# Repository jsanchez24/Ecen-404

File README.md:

# Ecen-404
Modulation Methods for Three-Phase Inverter

Control Subsystem
-avr_interface.v
-primary_side.v
-pulse.v
-pwm.v
-secondary_side.v
-serial_rx.v
-serial_tx.v
-spi_slave.v
-mojo_top.v

Sensor Subsytem
-Avanzato1.zip
-LM319.lbr
-LM319N.lbr
-Sensor Circuit.brb
-Sensor Circuit.sch
-TL081.lbr

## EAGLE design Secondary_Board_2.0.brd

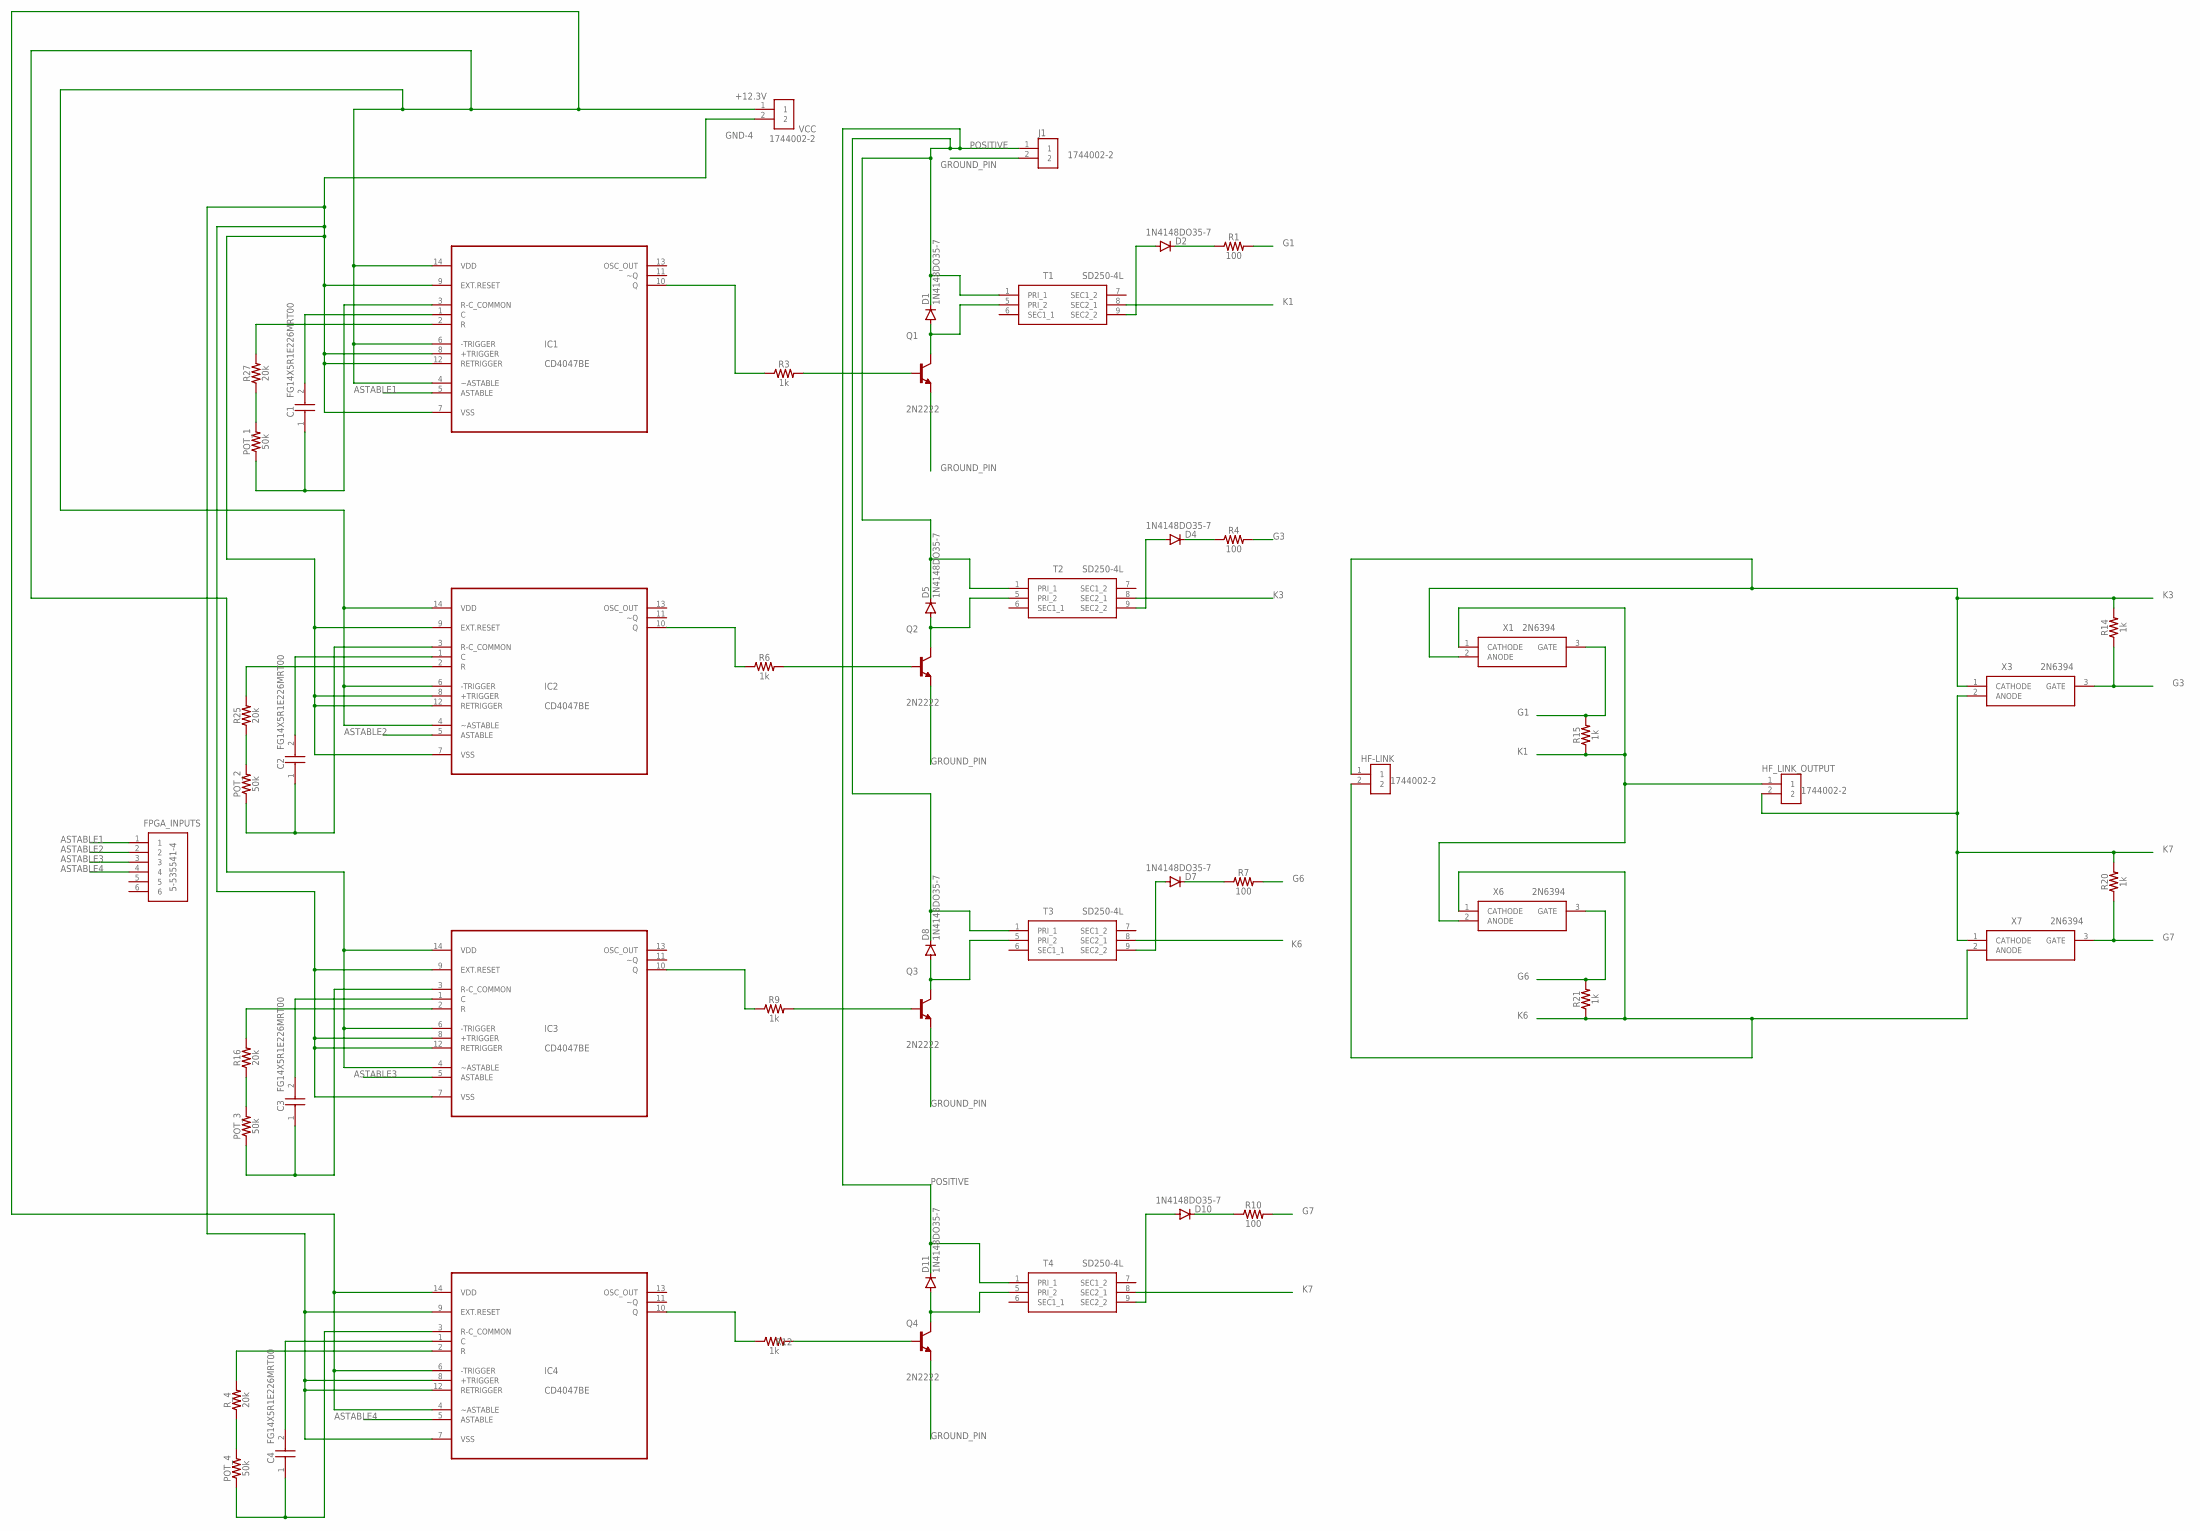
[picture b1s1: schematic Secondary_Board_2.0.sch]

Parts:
C1, C2, C3, C4: FG14X5R1E226MRT00; CAPPRD550W50D395H550
D1, D2, D4, D5, D7, D8, D10, D11: 1N4148DO35-7; DO35-7
FPGA_INPUTS: 5-535541-4; SHDR6W76P0X254_1X6_1524X356X62
HF-LINK: 1744002-2; CONN_1744002-2
HF_LINK_OUTPUT: 1744002-2; CONN_1744002-2
IC1, IC2, IC3, IC4: CD4047BE; DIP254P762X508-14
J1: 1744002-2; CONN_1744002-2
POT_1, POT_2, POT_3, POT_4: 50k; AXIAL-0.3
Q1, Q2, Q3, Q4: 2N2222; TO127P584H533-3
R1, R4, R7, R10: 100; AXIAL-0.3
R3, R6, R9, R12, R14, R15, R20, R21: 1k; AXIAL-0.3
R16, R25, R27: 20k; AXIAL-0.3
R_4: 20k; AXIAL-0.3
T1, T2, T3, T4: SD250-4L; SD2504L
VCC: 1744002-2; CONN_1744002-2
X1, X3, X6, X7: 2N6394; TO254P482X997X2018-3P

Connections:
+12.3V: IC1.4 (~ASTABLE), IC1.6 (-TRIGGER), IC1.14 (VDD), IC2.4 (~ASTABLE), IC2.6 (-TRIGGER), IC2.14 (VDD), IC3.4 (~ASTABLE), IC3.6 (-TRIGGER), IC3.14 (VDD), IC4.4 (~ASTABLE), IC4.6 (-TRIGGER), IC4.14 (VDD), VCC.1
ASTABLE1: FPGA_INPUTS.1, IC1.5 (ASTABLE)
ASTABLE2: FPGA_INPUTS.2, IC2.5 (ASTABLE)
ASTABLE3: FPGA_INPUTS.3, IC3.5 (ASTABLE)
ASTABLE4: FPGA_INPUTS.4, IC4.5 (ASTABLE)
G1: R1.P$2 (2), R15.P$2 (2), X1.3 (GATE)
G3: R4.P$2 (2), R14.P$1 (1), X3.3 (GATE)
G6: R7.P$2 (2), R21.P$2 (2), X6.3 (GATE)
G7: R10.P$2 (2), R20.P$1 (1), X7.3 (GATE)
GND-4: IC1.7 (VSS), IC1.8 (+TRIGGER), IC1.9 (EXT.RESET), IC1.12 (RETRIGGER), IC2.7 (VSS), IC2.8 (+TRIGGER), IC2.9 (EXT.RESET), IC2.12 (RETRIGGER), IC3.7 (VSS), IC3.8 (+TRIGGER), IC3.9 (EXT.RESET), IC3.12 (RETRIGGER), IC4.7 (VSS), IC4.8 (+TRIGGER), IC4.9 (EXT.RESET), IC4.12 (RETRIGGER), VCC.2
GROUND_PIN: J1.2, Q1.1 (E), Q2.1 (E), Q3.1 (E), Q4.1 (E)
K1: HF_LINK_OUTPUT.1, R15.P$1 (1), T1.8 (SEC2_1), X1.1 (CATHODE), X6.2 (ANODE)
K3: HF-LINK.1, R14.P$2 (2), T2.8 (SEC2_1), X1.2 (ANODE), X3.1 (CATHODE)
K6: HF-LINK.2, R21.P$1 (1), T3.8 (SEC2_1), X6.1 (CATHODE), X7.2 (ANODE)
K7: HF_LINK_OUTPUT.2, R20.P$2 (2), T4.8 (SEC2_1), X3.2 (ANODE), X7.1 (CATHODE)
unnamed: D5.A, Q2.3 (C), T2.5 (PRI_2)
unnamed: D1.A, Q1.3 (C), T1.5 (PRI_2)
unnamed: D2.C, R1.P$1 (1)
unnamed: IC1.10 (Q), R3.P$1 (1)
unnamed: Q1.2 (B), R3.P$2 (2)
unnamed: D4.A, T2.9 (SEC2_2)
unnamed: IC2.10 (Q), R6.P$1 (1)
unnamed: IC3.10 (Q), R9.P$1 (1)
unnamed: IC4.10 (Q), R12.P$1 (1)
unnamed: D4.C, R4.P$1 (1)
unnamed: D7.A, T3.9 (SEC2_2)
unnamed: Q2.2 (B), R6.P$2 (2)
unnamed: D10.A, T4.9 (SEC2_2)
unnamed: D2.A, T1.9 (SEC2_2)
unnamed: D8.A, Q3.3 (C), T3.5 (PRI_2)
unnamed: D7.C, R7.P$1 (1)
unnamed: IC1.2 (R), R27.P$2 (2)
unnamed: POT_1.P$2 (2), R27.P$1 (1)
unnamed: C1.2 (-), IC1.1 (C)
unnamed: C1.1 (+), IC1.3 (R-C_COMMON), POT_1.P$1 (1)
unnamed: IC2.2 (R), R25.P$2 (2)
unnamed: POT_2.P$2 (2), R25.P$1 (1)
unnamed: C2.2 (-), IC2.1 (C)
unnamed: Q3.2 (B), R9.P$2 (2)
unnamed: C2.1 (+), IC2.3 (R-C_COMMON), POT_2.P$1 (1)
unnamed: D11.A, Q4.3 (C), T4.5 (PRI_2)
unnamed: D10.C, R10.P$1 (1)
unnamed: IC3.2 (R), R16.P$2 (2)
unnamed: Q4.2 (B), R12.P$2 (2)
unnamed: POT_3.P$2 (2), R16.P$1 (1)
unnamed: C3.2 (-), IC3.1 (C)
unnamed: C3.1 (+), IC3.3 (R-C_COMMON), POT_3.P$1 (1)
unnamed: IC4.2 (R), R_4.P$2 (2)
unnamed: POT_4.P$2 (2), R_4.P$1 (1)
unnamed: C4.2 (-), IC4.1 (C)
unnamed: C4.1 (+), IC4.3 (R-C_COMMON), POT_4.P$1 (1)
POSITIVE: D1.C, D5.C, D8.C, D11.C, J1.1, T1.1 (PRI_1), T2.1 (PRI_1), T3.1 (PRI_1), T4.1 (PRI_1)

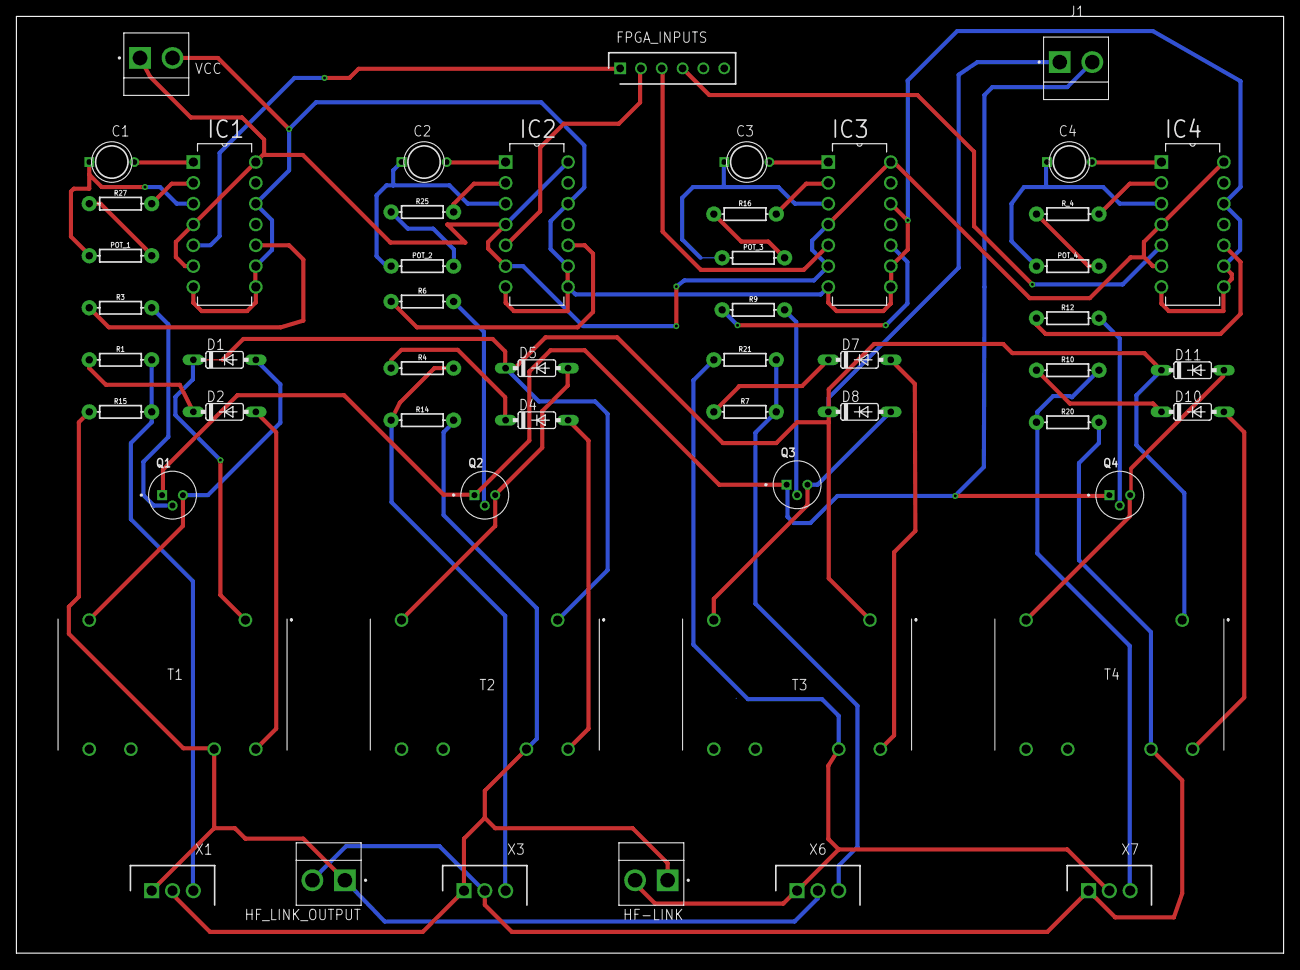
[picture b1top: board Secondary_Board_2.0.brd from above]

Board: 2 copper layers, 154.6 x 114.3 mm, 53 parts (0 on the bottom side), 52 nets.

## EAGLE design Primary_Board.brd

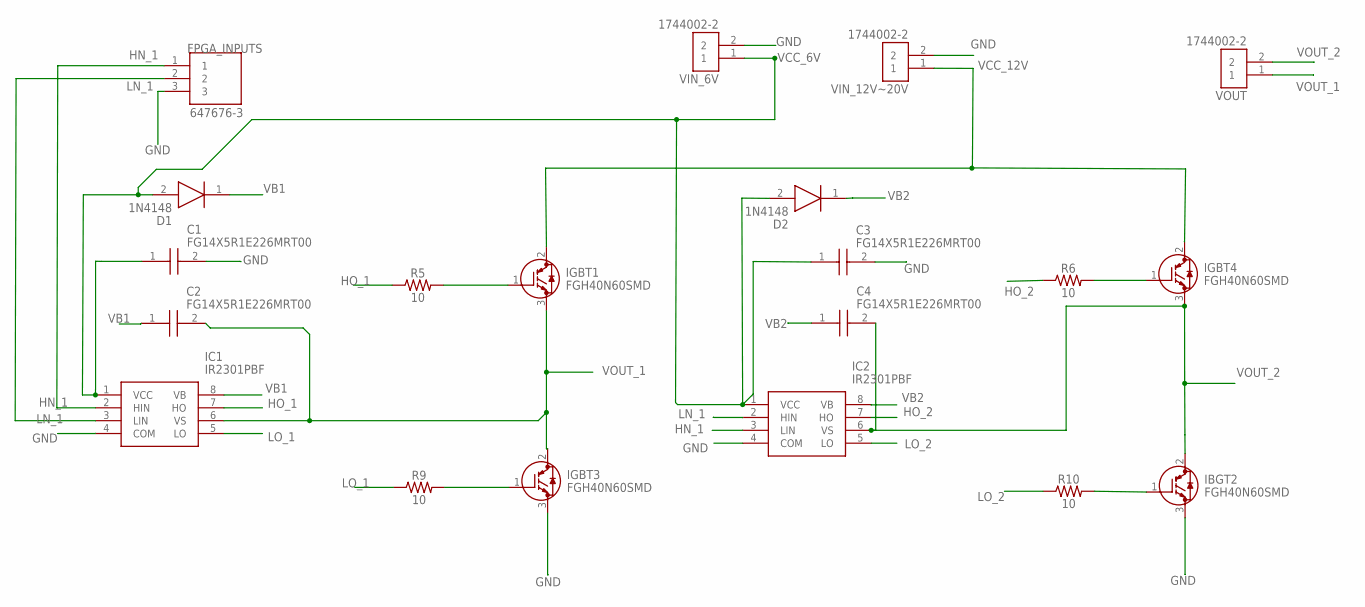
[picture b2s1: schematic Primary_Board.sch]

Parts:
C1, C2, C3, C4: FG14X5R1E226MRT00; CAPPRD550W50D395H550
D1, D2: 1N4148; DIOAD1068W53L380D172
FPGA_INPUTS: 647676-3; TE_647676-3
IBGT2: FGH40N60SMD; TO556P482X1562X2475-3P
IC1, IC2: IR2301PBF; DIP762W56P254L988H533Q8N
IGBT1, IGBT3, IGBT4: FGH40N60SMD; TO556P482X1562X2475-3P
R5, R6, R9, R10: 10; AXIAL-0.3
VIN_6V, VIN_12V~20V: 1744002-2; CONN_1744002-2
VOUT: 1744002-2; CONN_1744002-2

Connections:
GND: C1.2 (-), C3.2 (-), FPGA_INPUTS.3, IBGT2.3 (E), IC1.4 (COM), IC2.4 (COM), IGBT3.3 (E), VIN_6V.2, VIN_12V~20V.2
HN_1: FPGA_INPUTS.1, IC1.2 (HIN), IC2.3 (LIN)
HO_1: IC1.7 (HO), R5.P$1 (1)
HO_2: IC2.7 (HO), R6.P$1 (1)
IGBT2: IBGT2.1 (G), R10.P$2 (2)
LN_1: FPGA_INPUTS.2, IC1.3 (LIN), IC2.2 (HIN)
LO_1: IC1.5 (LO), R9.P$1 (1)
LO_2: IC2.5 (LO), R10.P$1 (1)
unnamed: IGBT1.1 (G), R5.P$2 (2)
unnamed: IGBT4.1 (G), R6.P$2 (2)
unnamed: IGBT3.1 (G), R9.P$2 (2)
VB1: C2.1 (+), D1.1 (K), IC1.8 (VB)
VB2: C4.1 (+), D2.1 (K), IC2.8 (VB)
VCC_6V: C1.1 (+), C3.1 (+), D1.2 (A), D2.2 (A), IC1.1 (VCC), IC2.1 (VCC), VIN_6V.1
VCC_12V: IGBT1.2 (C), IGBT4.2 (C), VIN_12V~20V.1
VOUT_1: C2.2 (-), IC1.6 (VS), IGBT1.3 (E), IGBT3.2 (C), VOUT.1
VOUT_2: C4.2 (-), IBGT2.2 (C), IC2.6 (VS), IGBT4.3 (E), VOUT.2

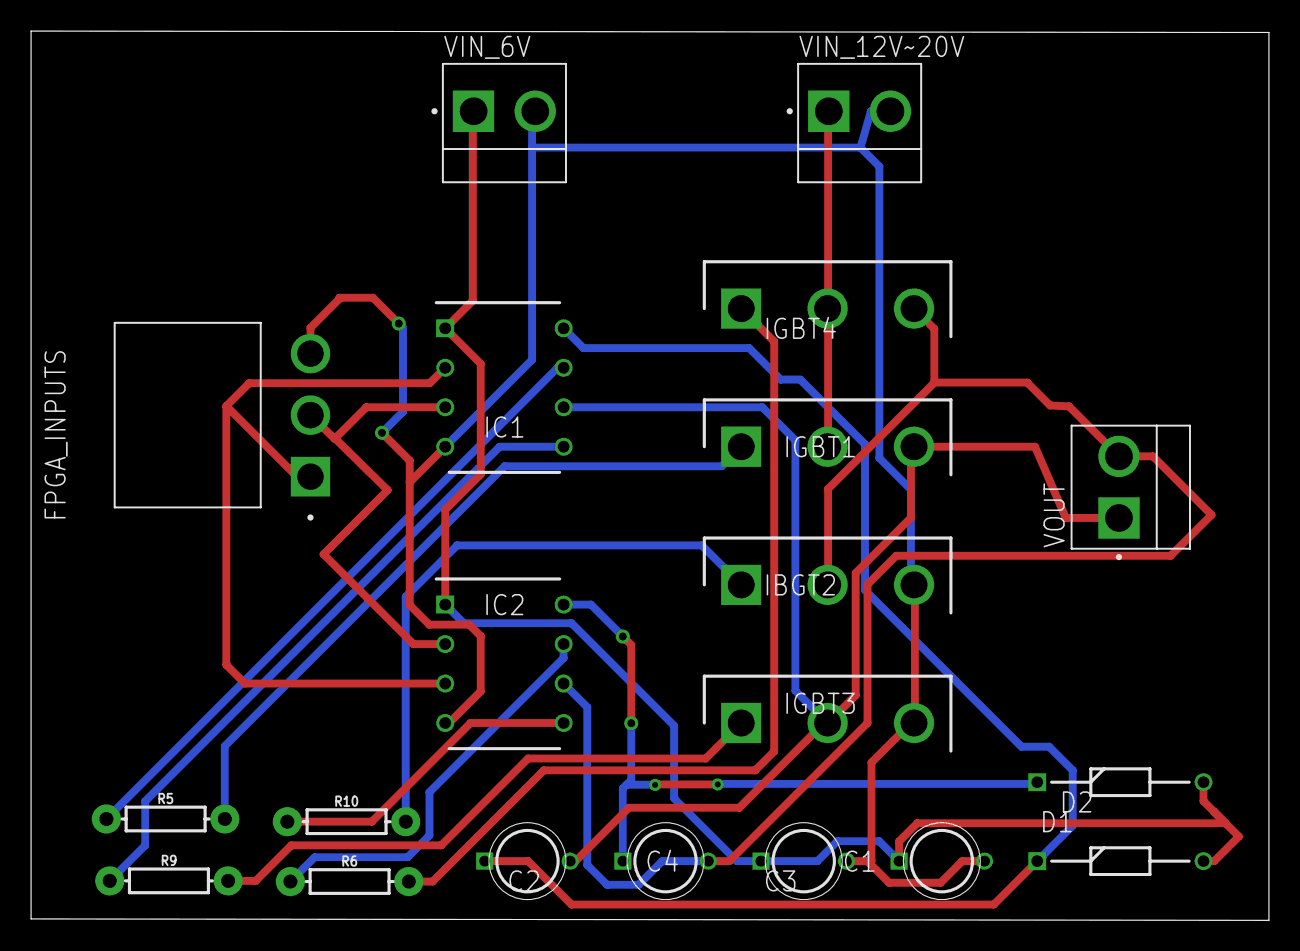
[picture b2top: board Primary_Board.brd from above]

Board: 2 copper layers, 79.7 x 57.2 mm, 20 parts (0 on the bottom side), 17 nets.

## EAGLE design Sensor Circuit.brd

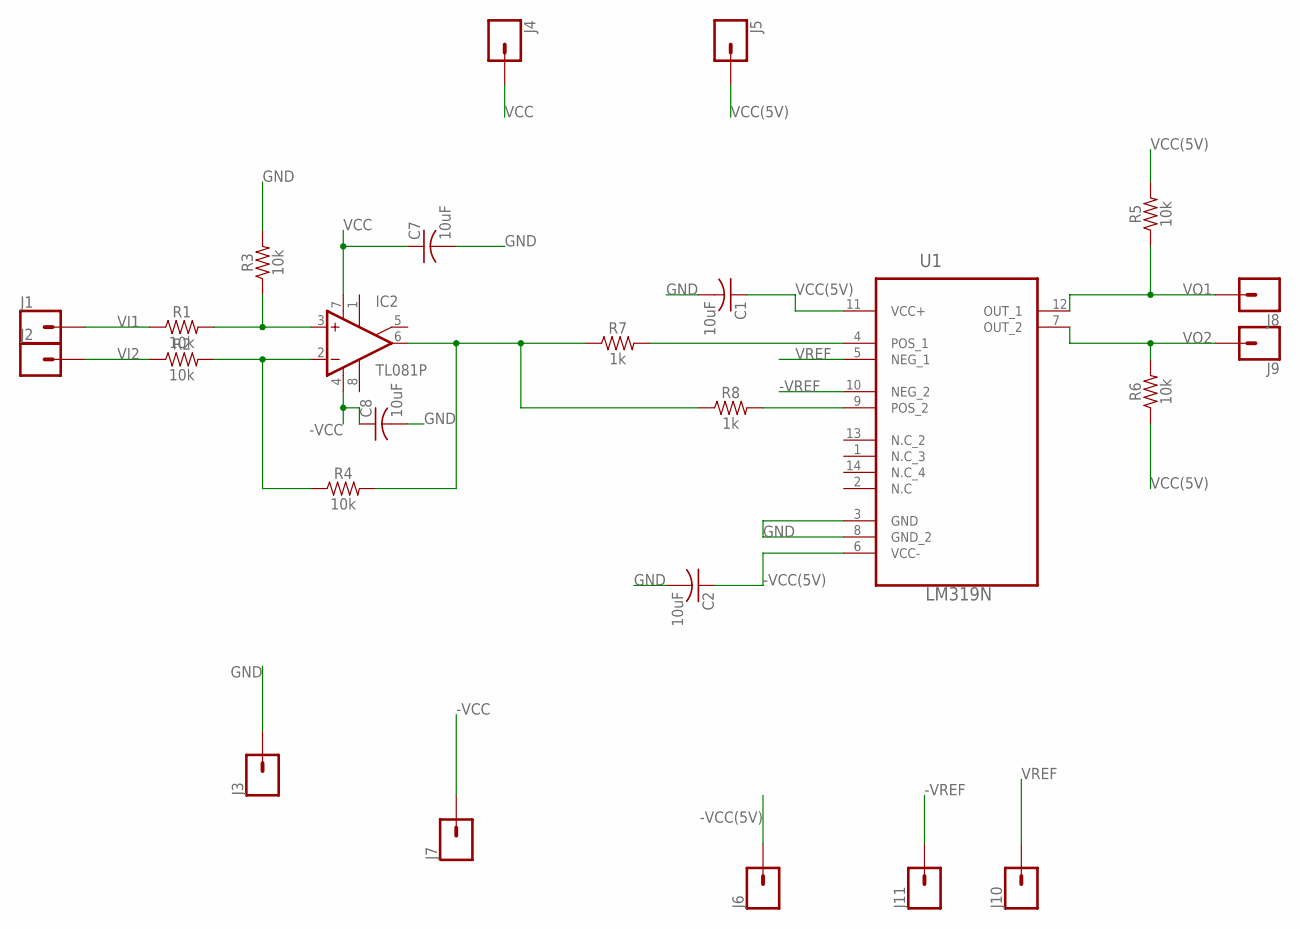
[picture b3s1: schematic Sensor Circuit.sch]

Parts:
C1, C2, C7, C8: 10uF; C050-024X044
IC2: TL081P; DIL08
J1, J2, J3, J4, J5, J6, J7, J8, J9, J10, J11: CONN_01; 1X01
R1, R2, R3, R4, R5, R6: 10k; AXIAL-0.3
R7, R8: 1k; AXIAL-0.3
U1: LM319N; DIP254P762X510-14

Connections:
-VCC: C8.1, IC2.4 (V-), J7.1
-VCC(5V): C2.1, J6.1, U1.6 (VCC-)
-VREF: J11.1, U1.10 (NEG_2)
GND: C1.2, C2.2, C7.2, C8.2, J3.1, R3.P$2 (2), U1.3 (GND), U1.8 (GND_2)
unnamed: IC2.2 (-IN), R2.P$2 (2), R4.P$1 (1)
unnamed: IC2.6 (OUT), R4.P$2 (2), R7.P$1 (1), R8.P$1 (1)
unnamed: IC2.3 (+IN), R1.P$2 (2), R3.P$1 (1)
unnamed: R8.P$2 (2), U1.9 (POS_2)
unnamed: R7.P$2 (2), U1.4 (POS_1)
VCC: C7.1, IC2.7 (V+), J4.1
VCC(5V): C1.1, J5.1, R5.P$2 (2), R6.P$1 (1), U1.11 (VCC+)
VI1: J1.1, R1.P$1 (1)
VI2: J2.1, R2.P$1 (1)
VO1: J8.1, R5.P$1 (1), U1.12 (OUT_1)
VO2: J9.1, R6.P$2 (2), U1.7 (OUT_2)
VREF: J10.1, U1.5 (NEG_1)

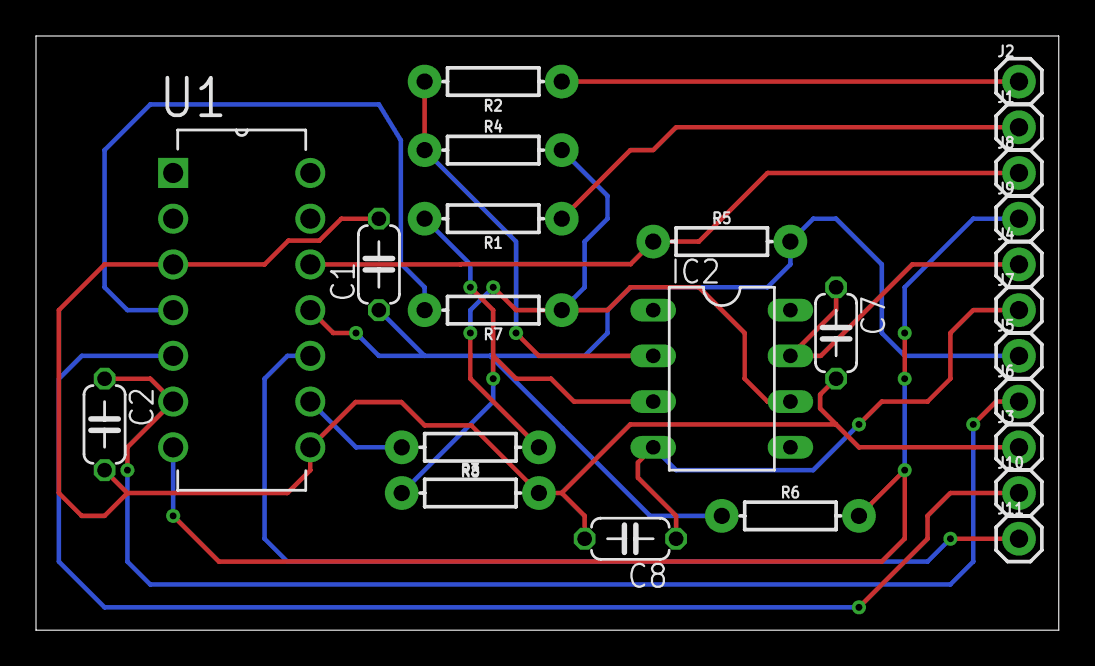
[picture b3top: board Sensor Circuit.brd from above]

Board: 2 copper layers, 56.8 x 33.0 mm, 25 parts (0 on the bottom side), 16 nets.

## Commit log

2019-08-26 Rename Micro Controller - avr_interface.v to Micro Controller Code - avr_interface.v
2019-09-05 Create Weekly Updates
2019-09-05 Update Weekly Updates

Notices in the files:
parts and their libraries:
SparkFun-Resistors: Licensing: Creative Commons ShareAlike 4.0 International - https://creativecommons.org/licenses/by-sa/4.0
